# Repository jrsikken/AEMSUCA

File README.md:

# AEMSUCA
The AEMSUCA is a 15x20mm board for the AEM10941 Solar Harvesting IC from E-peas. It efficiently converts solar panel energy into SUperCApacitor charge, it even works with indoor light. It features two regulated outputs that are enabled when the supercapacitor has sufficient charge, and a low voltage warning that informs the user of impending shutdown when the supercapacitors run low. It easily integrates in other projects because of the castellated via's, and when soldered onto 0.1' pitch header it fits in a bread board.

I sell this board on Tindie. https://www.tindie.com/products/jaspersikken/solar-harvesting-into-supercapacitors/

This project is on Hackaday https://hackaday.io/project/160470/

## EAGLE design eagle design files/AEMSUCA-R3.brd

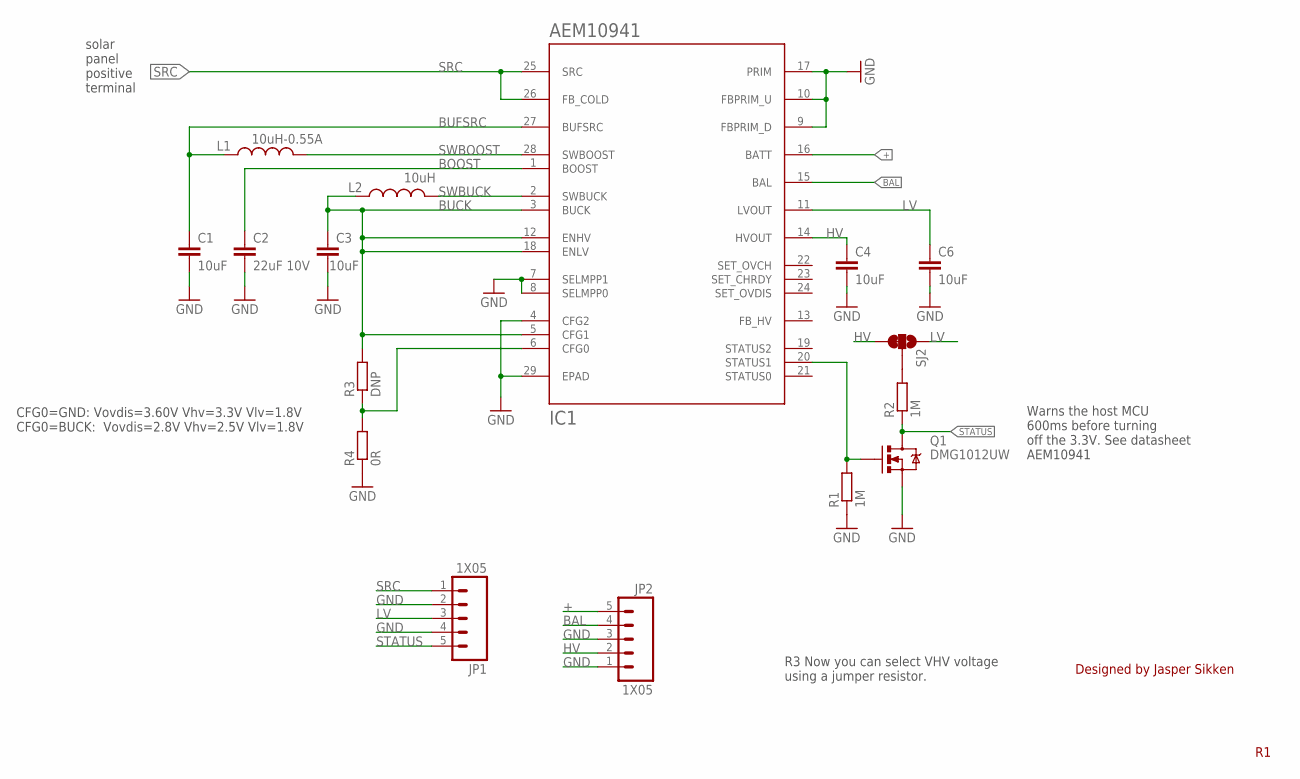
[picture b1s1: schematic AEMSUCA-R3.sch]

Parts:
C1, C3, C4, C6: 10uF; C0603
C2: 22uF 10V; C0603
IC1: AEM10941; QFN50P505X505X90-28
JP1, JP2: 1X05; 1X05_2.54MM_ROUND_NOSILK
L1: 10uH-0.55A; LPS4012
L2: 10uH; L0603
Q1: DMG1012UW; SOT323
R1, R2: 1M; R0402
R3: DNP; R0402
R4: 0R; R0402
SJ2: SOLDERJUMPER_3WAY_12SHORT3WAY; SJ_3S_NC_0402

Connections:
+: IC1.16 (BATT), JP2.5
BAL: IC1.15 (BAL), JP2.4
BOOST: C2.1, IC1.1 (BOOST)
BUCK: C3.1, IC1.3 (BUCK), IC1.5 (CFG1), IC1.12 (ENHV), IC1.18 (ENLV), L2.1, R3.2
BUFSRC: C1.1, IC1.27 (BUFSRC), L1.1
GND: C1.2, C2.2, C3.2, C4.2, C6.2, IC1.4 (CFG2), IC1.7 (SELMPP1), IC1.8 (SELMPP0), IC1.9 (FBPRIM_D), IC1.10 (FBPRIM_U), IC1.17 (PRIM), IC1.29 (EPAD), JP1.2, JP1.4, JP2.1, JP2.3, Q1.2 (S), R1.1, R4.1
HV: C4.1, IC1.14 (HVOUT), JP2.2, SJ2.1
LV: C6.1, IC1.11 (LVOUT), JP1.3, SJ2.3
unnamed: R2.2, SJ2.2
unnamed: IC1.6 (CFG0), R3.1, R4.2
SRC: IC1.25 (SRC), IC1.26 (FB_COLD), JP1.1
STATUS: JP1.5, Q1.3 (D), R2.1
STATUS1: IC1.20 (STATUS1), Q1.1 (G), R1.2
SWBOOST: IC1.28 (SWBOOST), L1.2
SWBUCK: IC1.2 (SWBUCK), L2.2

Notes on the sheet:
Warns the host MCU 600ms before turning off the 3.3V. See datasheet AEM10941
Designed by Jasper Sikken
solar panel positive terminal
R3 Now you can select VHV voltage using a jumper resistor.
CFG0=GND: Vovdis=3.60V Vhv=3.3V Vlv=1.8V CFG0=BUCK: Vovdis=2.8V Vhv=2.5V Vlv=1.8V

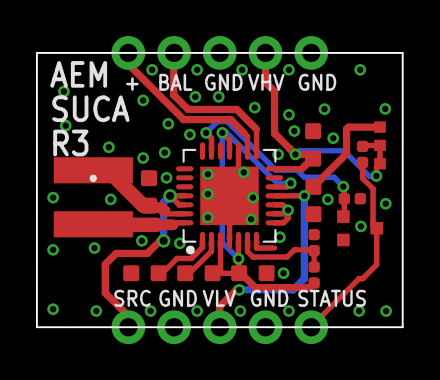
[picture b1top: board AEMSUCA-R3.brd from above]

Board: 2 copper layers, 20.3 x 15.2 mm, 16 parts (0 on the bottom side), 15 nets.

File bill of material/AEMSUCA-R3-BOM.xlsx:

Reference | QTY | Value | Package | Manufacturer | Manufacturer Part number | Description | Tolerance | Voltage | Dielectric
C1,C3, C4, C6 | 4 | 10uF | C0603 | Generic part | Generic part | capacitor | 0.2 | 10V | X5R
C2 | 1 | 22uF | C0603 | Generic part | Generic part | capacitor | 0.05 | 10V | X5R
L1 | 1 | 10uH-0.55A | LPS4012 | COILCRAFT | LPS4012-103MRB | inductor
L2 | 1 | 10uH | L0603 | TDK | MLZ1608M100WT | inductor | 0.2 | 0.25A
R1, R2 | 2 | 1M | R0402 | Generic part | Generic part | resistor | 0.05
R3 | 0 | Do not place | Do not place | Do not place | Do not place | Do not place
R4 | 1 | 0R | R0402 | Generic part | Generic part | resistor | 0.05
Q1 | 1 | DMG1012UW-7 | SOT323 | Diodes | DMG1012UW-7 | mosfet
IC1 | 1 | AEM10941 | QFN50P505X50 | E-peas | AEM10941 | IC

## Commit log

2018-09-16 Update LICENSE
2018-09-16 Added files for R2
2018-11-09 added schematic in pdf format
2018-11-27 updated PCB and gerbers to reduce solderpaste under IC1 to 50%
2019-05-28 specified L2 manufacturer and part number in Bill of Materials
2020-11-29 Add files via upload
    After ordering R3
2020-12-26 Corrected position of R4
